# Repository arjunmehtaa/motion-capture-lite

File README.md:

# Motion Capture Lite
Project created as part of the FYDP Capstone (ECE 2024).

Created by: Arjun Mehta, Aryaman Singh, Kevin Kalathil, Nicolas Bao

## Project Abstract
The objective of this project is to build a “lite” motion-capture device that can accurately track small objects that are normally too difficult to track using just a camera. The device uses semi-passive imperceptible markers, which refer to projectors that illuminate small LED marker tags placed on objects. The marker tags are equipped with photosensors to detect light from a projector, and a microcontroller. The markers will process and communicate the results back to a computer where a software tool, through signal processing, converts recorded motion data from the device into 3D motion vectors and allows for real-time tracking.

## Files
- `README.md`: This file.
- `report.pdf`: The final report for the project.
- `poster.pdf`: Poster for Capstone Presentation.

- `beamer_wifi.ino`: Arduino code for the beamers
- `tag_wifi.ino`: Arduino code for the tags
  
- `udp_server.py`: Python code for the server (receives data from the tags)
- `udp_server_calibrate.py`: Optional tool to help calibrate the system
- `visualizer.py`: 3D Visualization tool for tag motion (requires `matplotlib`)

- `rust_sender/*`: Rust code for the sender (sends data to the tags)

- `schematics/*`: Schematics for the project (tag and beamer)
- `old/*`: Old code and files - please ignore!

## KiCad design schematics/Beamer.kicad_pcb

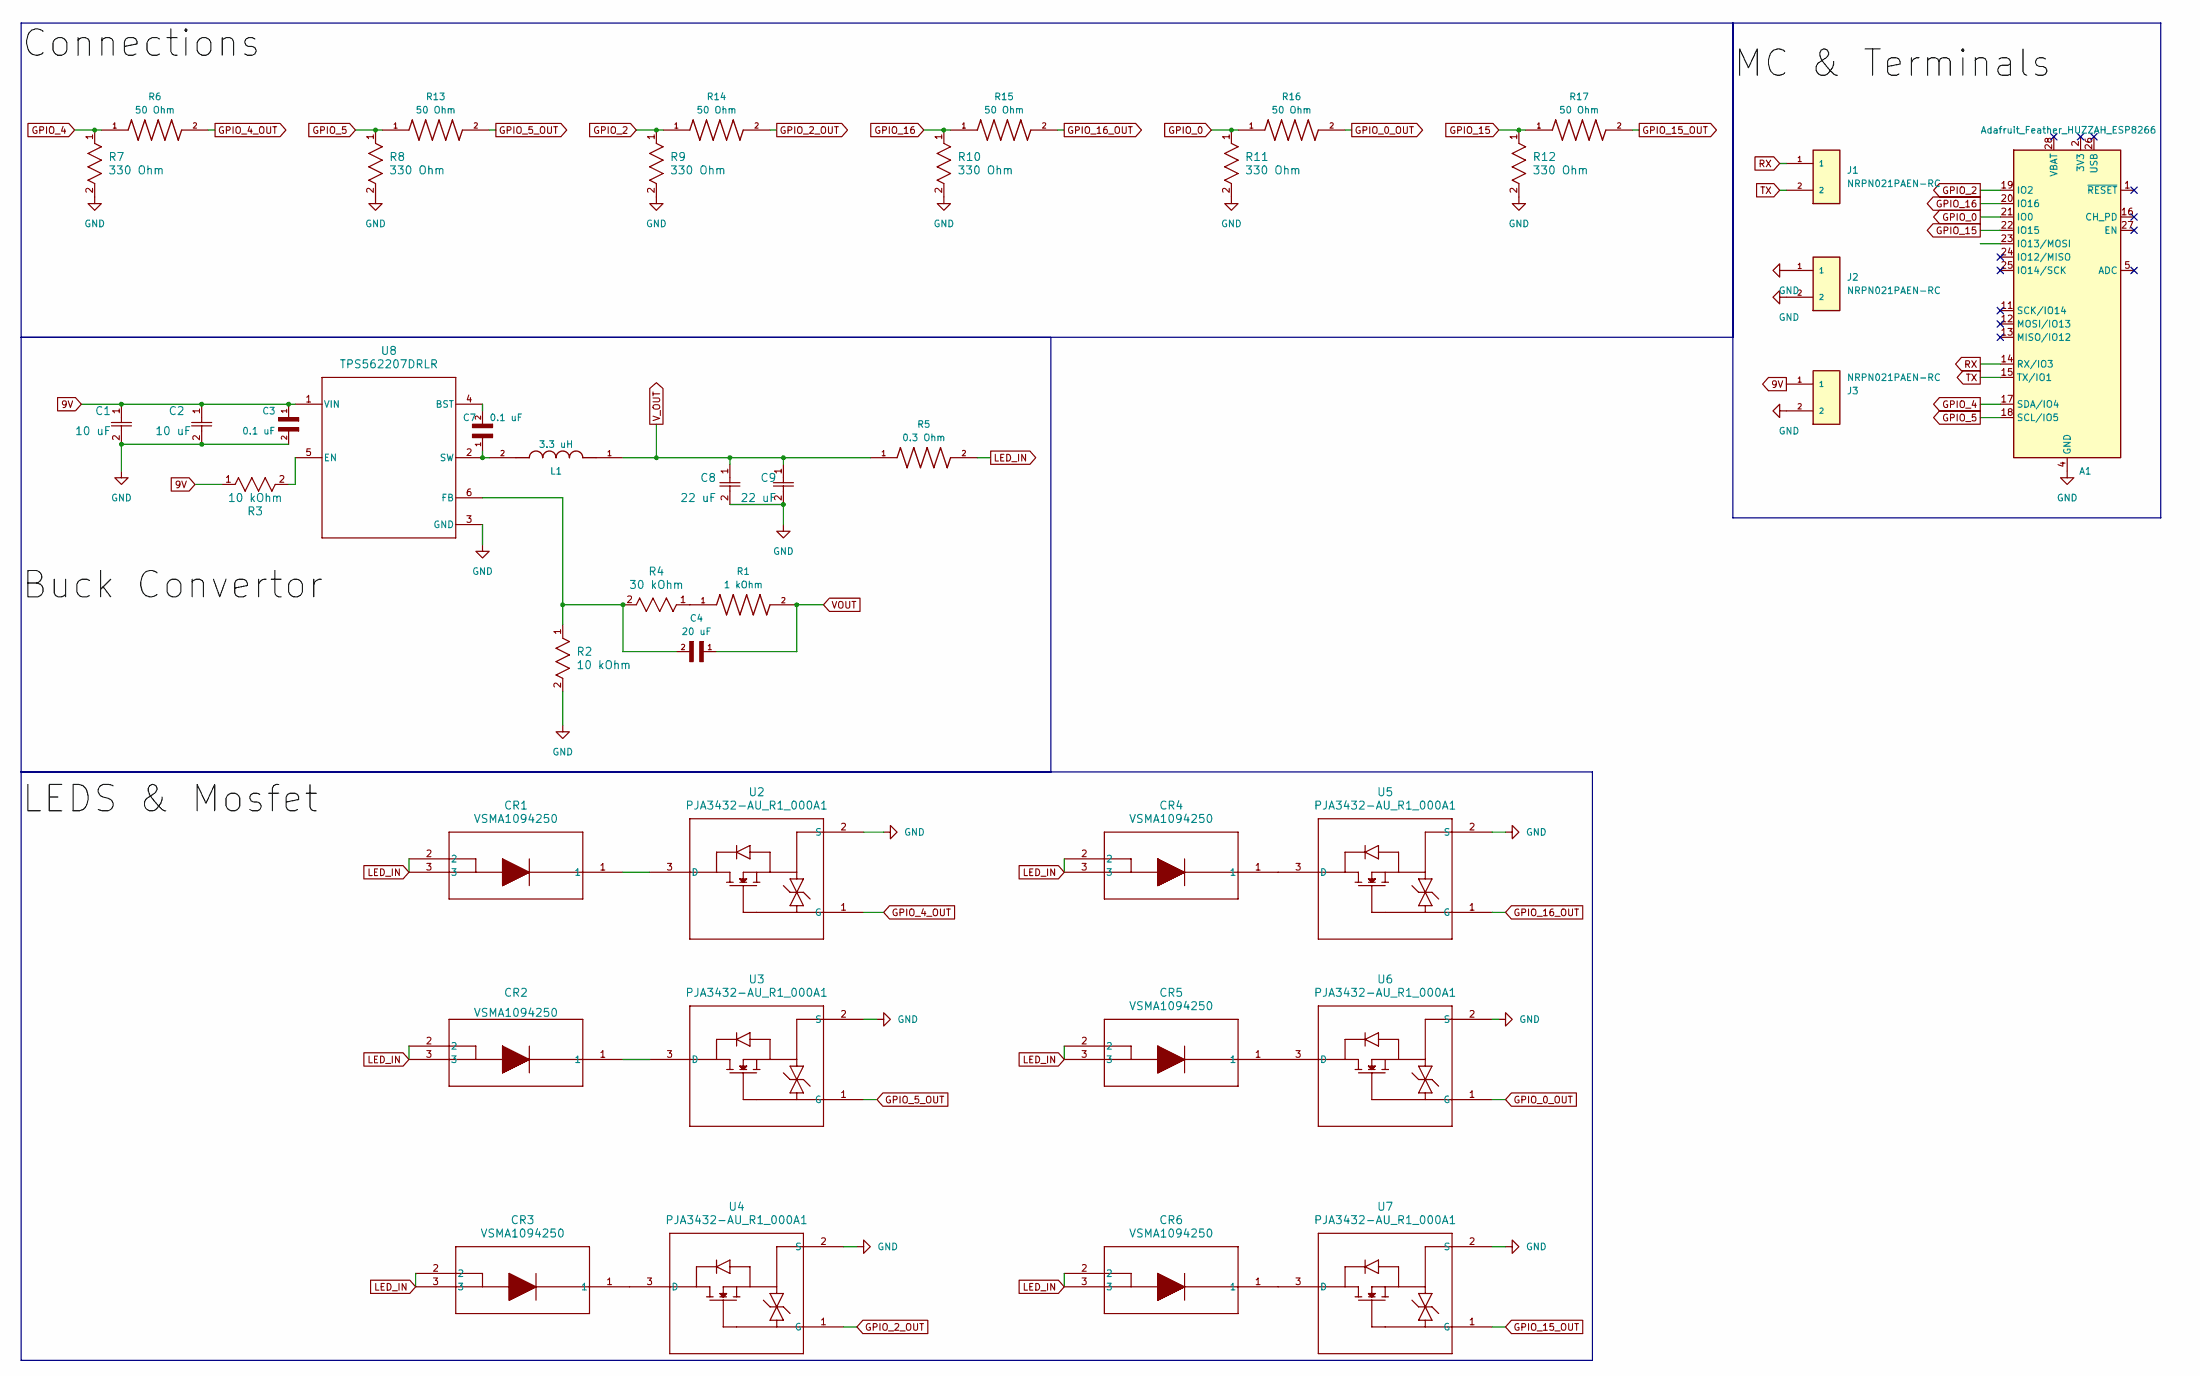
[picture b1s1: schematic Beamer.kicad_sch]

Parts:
A1: Adafruit_Feather_HUZZAH_ESP8266; Adafruit_Feather
C1, C2: 10 uF; C_0805_2012Metric_Pad1.18x1.45mm_HandSolder
C3, C7: 0.1 uF; C_0402_1005Metric_Pad0.74x0.62mm_HandSolder
C4: 20 uF; CAPC1810X80N
C8, C9: 22 uF; C_0603_1608Metric_Pad1.08x0.95mm_HandSolder
CR1, CR2, CR3, CR4, CR5, CR6: VSMA1094250; DIODE_VSMA1094250_VIS
J1, J2, J3: NRPN021PAEN-RC; PinHeader_1x02_P2.00mm_Vertical; PARTREV E
L1: 3.3 uH; IND_ASPI-4020S-3R3M-T; PARTREV 03.07.13
R1: 1 kOhm; R_0603_1608Metric_Pad0.98x0.95mm_HandSolder
R2, R3: 10 kOhm; R_0402_1005Metric_Pad0.72x0.64mm_HandSolder
R4: 30 kOhm; R_0402_1005Metric_Pad0.72x0.64mm_HandSolder
R5: 0.3 Ohm; R_0805_2012Metric_Pad1.20x1.40mm_HandSolder; PARTREV 3/1/2020
R6, R13, R14, R15, R16, R17: 50 Ohm; R_0603_1608Metric_Pad0.98x0.95mm_HandSolder
R7, R8, R9, R10, R11, R12: 330 Ohm; R_0603_1608Metric_Pad0.98x0.95mm_HandSolder
U2, U3, U4, U5, U6, U7: PJA3432-AU_R1_000A1; SOT-23-3
U8: TPS562207DRLR; SOT-666

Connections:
9V: C1.1, C2.1, C3.1, J3.1, R3.1, U8.1 (VIN)
GND: A1.4 (GND), C1.2, C2.2, C3.2, C8.2, C9.2, J2.1, J2.2, J3.2, R2.2, R7.2, R8.2, R9.2, R10.2, R11.2, R12.2, U2.2 (S), U3.2 (S), U4.2 (S), U5.2 (S), U6.2 (S), U7.2 (S), U8.3 (GND)
GPIO_0: A1.21 (IO0), R11.1, R16.1
GPIO_0_OUT: R16.2, U6.1 (G)
GPIO_2: A1.19 (IO2), R9.1, R14.1
GPIO_2_OUT: R14.2, U4.1 (G)
GPIO_4: A1.17 (SDA/IO4), R6.1, R7.1
GPIO_4_OUT: R6.2, U2.1 (G)
GPIO_5: A1.18 (SCL/IO5), R8.1, R13.1
GPIO_5_OUT: R13.2, U3.1 (G)
GPIO_15: A1.22 (IO15), R12.1, R17.1
GPIO_15_OUT: R17.2, U7.1 (G)
GPIO_16: A1.20 (IO16), R10.1, R15.1
GPIO_16_OUT: R15.2, U5.1 (G)
LED_IN: CR1.2, CR1.3, CR2.2, CR2.3, CR3.2, CR3.3, CR4.2, CR4.3, CR5.2, CR5.3, CR6.2, CR6.3, R5.2
unnamed: R1.1, R4.1
unnamed: CR1.1, U2.3 (D)
unnamed: CR2.1, U3.3 (D)
unnamed: CR3.1, U4.3 (D)
unnamed: CR4.1, U5.3 (D)
unnamed: CR5.1, U6.3 (D)
unnamed: CR6.1, U7.3 (D)
unnamed: C7.2, U8.4 (BST)
unnamed: R3.2, U8.5 (EN)
unnamed: C4.2, R2.1, R4.2, U8.6 (FB)
unnamed: C7.1, L1.2, U8.2 (SW)
RX: A1.14 (RX/IO3), J1.1
TX: A1.15 (TX/IO1), J1.2

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
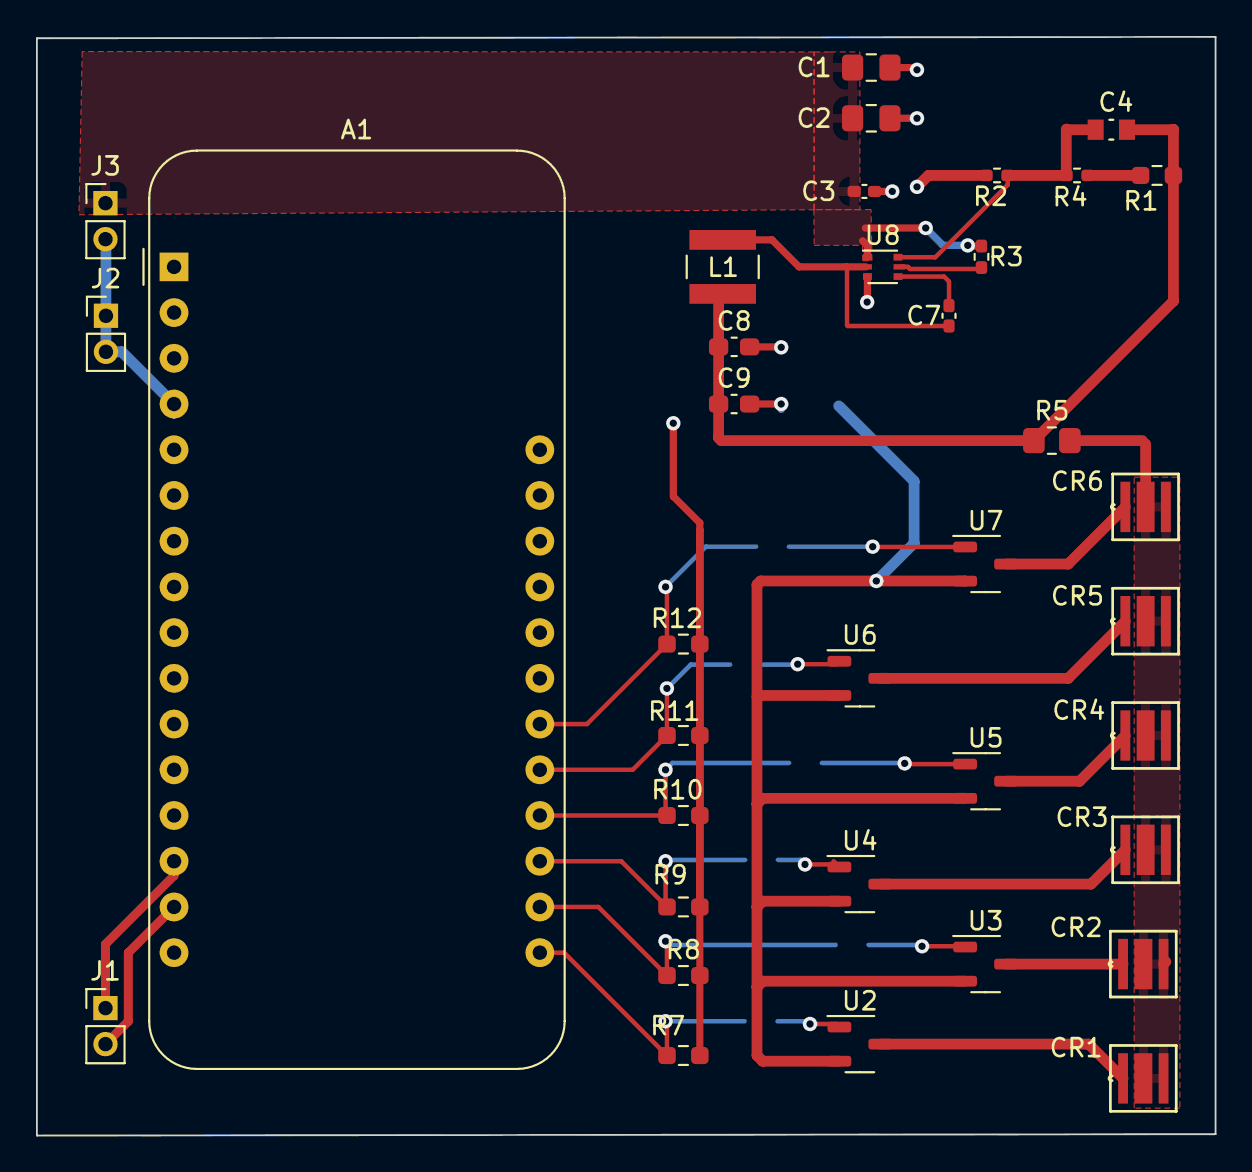
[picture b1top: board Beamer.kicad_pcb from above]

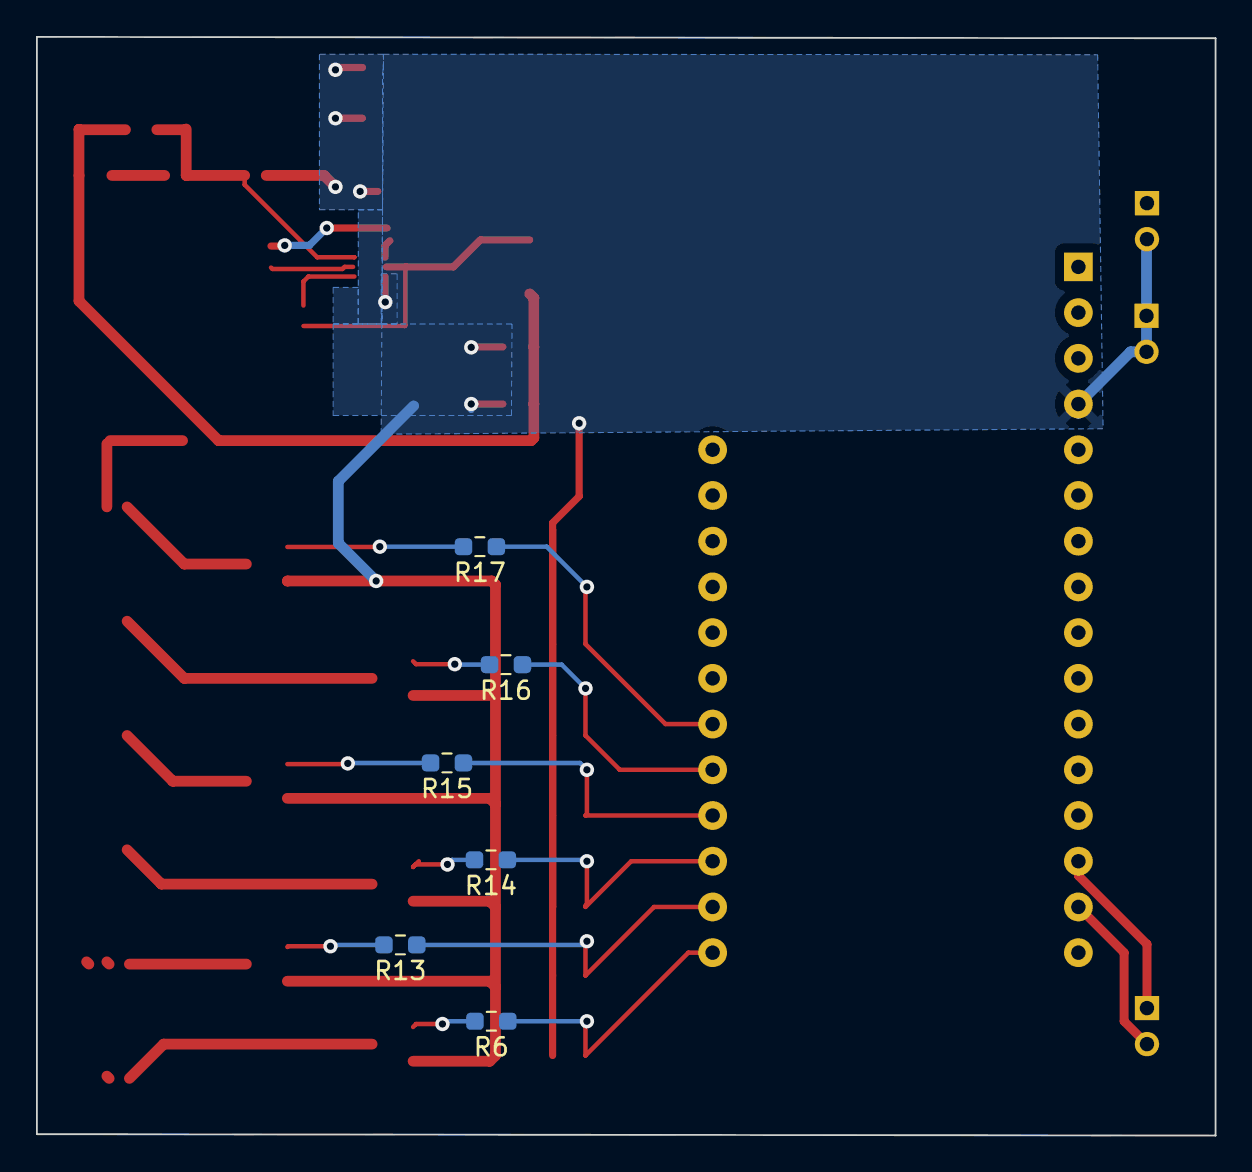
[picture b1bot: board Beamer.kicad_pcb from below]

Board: 2 copper layers, 65.5 x 61.0 mm, 42 parts (6 on the bottom side), 29 nets.

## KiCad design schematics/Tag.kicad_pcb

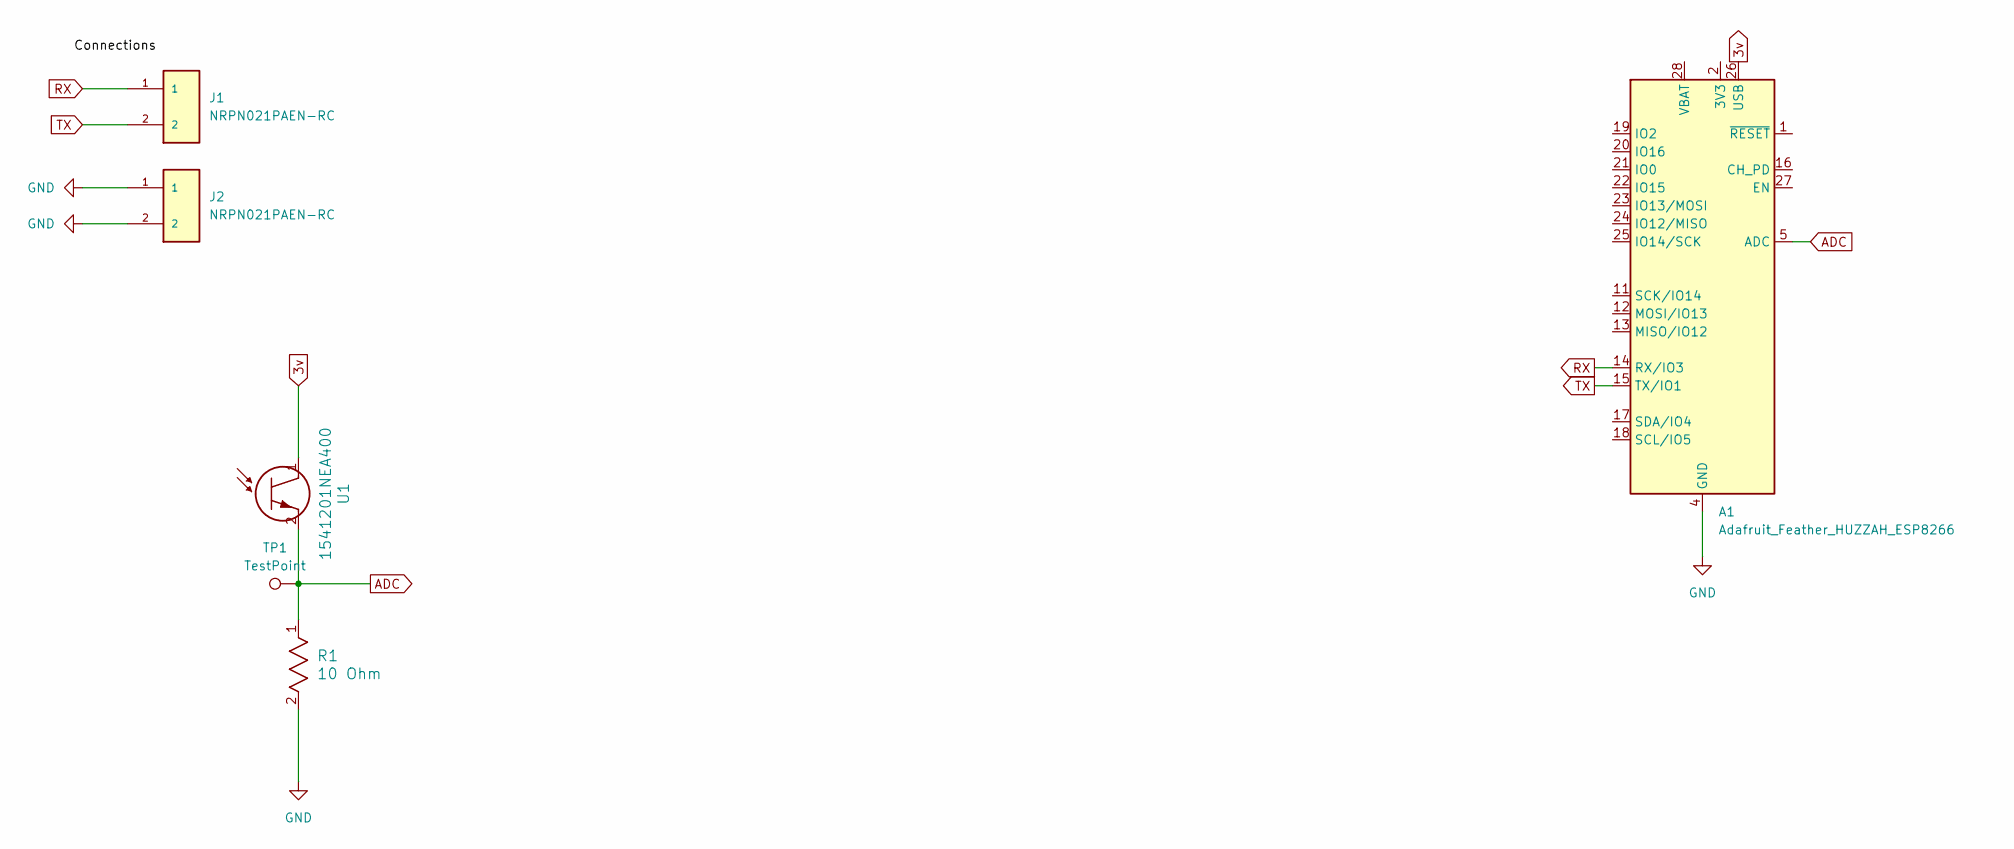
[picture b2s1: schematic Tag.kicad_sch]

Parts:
A1: Adafruit_Feather_HUZZAH_ESP8266; Adafruit_Feather
J1, J2: NRPN021PAEN-RC; PinHeader_1x02_P2.00mm_Vertical; PARTREV E
R1: 10 Ohm; R_0603_1608Metric_Pad0.98x0.95mm_HandSolder
TP1: TestPoint; TestPoint_Loop_D1.80mm_Drill1.0mm_Beaded
U1: 1541201NEA400; R_1206_3216Metric_Pad1.30x1.75mm_HandSolder

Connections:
3v: A1.26 (USB), U1.1
ADC: A1.5 (ADC), R1.1, TP1.1, U1.2
GND: A1.4 (GND), J2.1, J2.2, R1.2
RX: A1.14 (RX/IO3), J1.1
TX: A1.15 (TX/IO1), J1.2

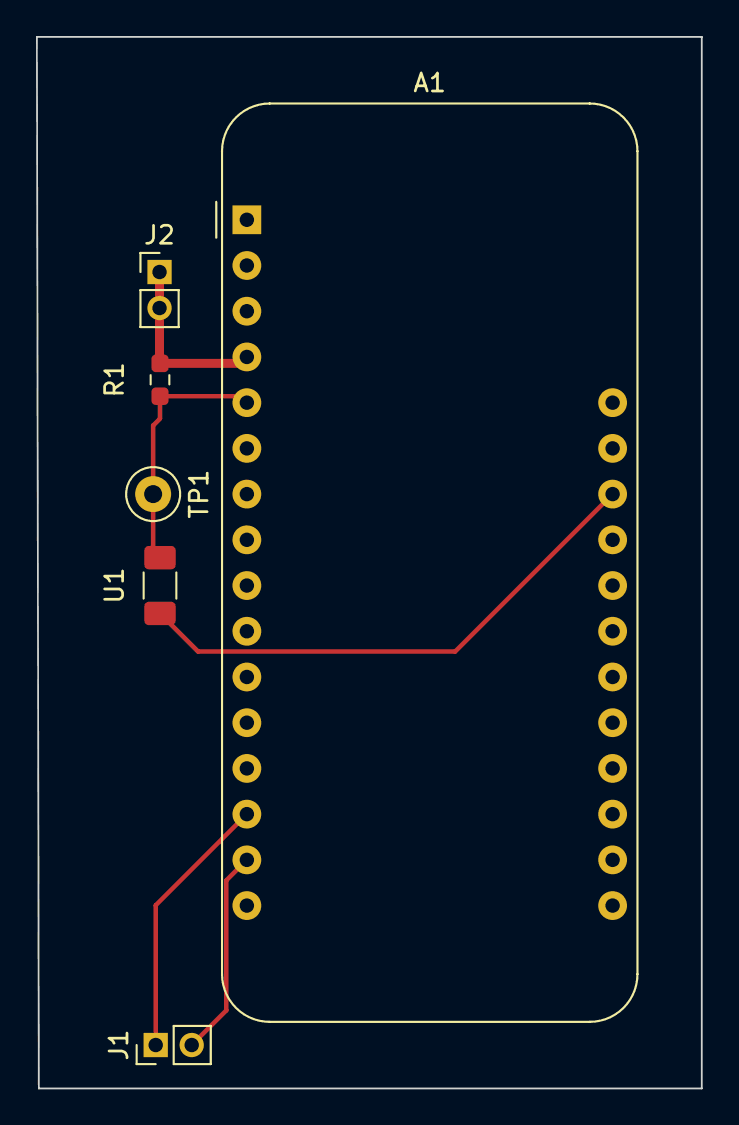
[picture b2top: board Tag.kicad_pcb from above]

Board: 2 copper layers, 36.9 x 58.4 mm, 6 parts (0 on the bottom side), 5 nets.

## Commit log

2023-06-11 Add 3D get_location, refactor code
2023-06-12 Refactor location.py
2023-06-13 Added basic Graycoding function
2023-06-15 Created orientation.py, reformatted code based on Python Black
2023-06-17 set up variables in orientation.py
2023-07-05 add arduino tag code
2023-07-08 Created beamer.ino, updated tag.ino
2023-07-08 Fixed small bug
2023-07-08 Fixed another bug
2023-07-08 ag comment 2
2023-07-17 graycoding fix
2023-07-18 UART_Testing for Tag (Manual Analog using voltage divider working)
2023-07-18 Message Passing for TAG
2023-07-22 Latest Tag Code (July 20)
2023-07-22 Tag: Loop3 + Beamer: Basic Setup without enable pin done
2023-07-24 getting data from serial
2023-07-24 wip monday 7:49PM
2023-07-27 ompute beamer angles
2023-07-27 receiving inputs from arduino
2023-07-27 rename to get_regions
2023-07-27 putting code directly within testing file
2023-07-27 restore old serial read file
2023-07-27 rm unused import
2023-07-27 rm unused function
2023-07-27 add newline
2023-07-27 add newlines
2023-07-28 Location now supports multiple tags
2023-07-28 BEAMER INTERRUPT WAITING
2023-07-28 2 tag 1 beamer
2024-01-10 Pending Changes: Jan 10
2024-01-10 Update gitignore
2024-01-25 Add WiFi files
2024-01-25 fix arduino_1
2024-01-25 use built-in LED for WiFi status
2024-01-25 update LED status indicator
2024-01-25 start listening and transmission sockets on separate threads
2024-02-08 add worker thread for handling received results and modify arduino response packet to round-trip received msg
2024-02-08 turn leds off on arduino once 100 msgs received to test one-way time
2024-02-08 rust multithreading implementation
2024-02-08 rust gui
2024-02-10 revert to working send/recieve
2024-02-13 testing: feb13
2024-02-13 working counter
2024-02-14 basic plot working
2024-02-14 basic 2D Visualization using random values
2024-02-15 demo: rust + python
2024-02-16 Tag wifi code
2024-02-16 change time to 20 ms
2024-02-20 update tag wifi code
2024-02-20 reduce print stmts
2024-02-20 Feb 20: Update Beamer WiFi Code
2024-02-20 remove old arduino files
2024-02-21 im sorry
2024-02-21 use a single sync for each cycle of 6 leds for the beamer
2024-02-21 change cycle time for server code
2024-02-21 fix errors
2024-02-22 basic 3d python visualization
2024-02-22 update beamer and tag wifi with sequencing
2024-02-25 Updated beamer and tag code - 24 feb
2024-02-25 Update Python Visualization
2024-02-26 async
2024-02-27 update beamer and tag feb 26
2024-02-28 wifi write to vec
2024-02-28 files from 2 days ago
2024-02-29 beamer: account for early sync, WiFi: vector prints
2024-02-29 tag sends 18 results to server
2024-02-29 Seperated WiFi Code
2024-03-02 friday coding
2024-03-03 March 2 Testing
2024-03-03 1D Visualization with 4 edge case handled
2024-03-03 Beamer uses 4 LEDs,
2024-03-03 2d testing using trigno AAAAHHHH
2024-03-04 added test, fixed regions, aaaahhhhhhh
2024-03-04 Switch to 5 beamrs
2024-03-04 WIP - 1
2024-03-04 before visualization
2024-03-05 nice 2d
2024-03-05 fix 15 with animate
2024-03-05 After Final Demo
2024-03-30 final demo changes
2024-05-11 Restructure Repository
2024-06-07 Rename Beamer_box_complete.3mf to Beamer_Model.3mf
